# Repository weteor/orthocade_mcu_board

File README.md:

# orthocade series mcu board

this is a mcu daughterboard used for some keyboards from the orthocade series, namely [Dig Dug](https://github.com/weteor/DigDug), [Brk Out](https://github.com/weteor/BrkOut) and [Froggr](https://github.com/weteor/Froggr).

## Want/Need one?

production files can be found [here](./prod). The cases are designed for 1.2mm pcbs, but also work with  1.6mm pcbs without problems.

You will need the following parts to build one:

- 1x capacitor - 0805 - 100nF

- 3x resistor -  0805 - 10kOhm

- 1x PCA9555 or TCA9555 IO-Expander

- 1x 20pin 0.5mm pitch FCC/FCP Connector

- 1x either Seeed Xiao RP2040 or Seeed Xiao BLE controller

optionally if you want to use BLE w/ battery:

- 1x battery connectro 2pin Molex Pico Blade
- 1x on/off switch MSK-12C02

### the rest

Everything in this repository is free to use however you might see fit. If you want to support me and my projects, please consider linking back to this repository if you build/change/use anything.

If you would like to send me a tip, you could do it [here](https://ko-fi.com/weteor) (Please don't feel like you have to).

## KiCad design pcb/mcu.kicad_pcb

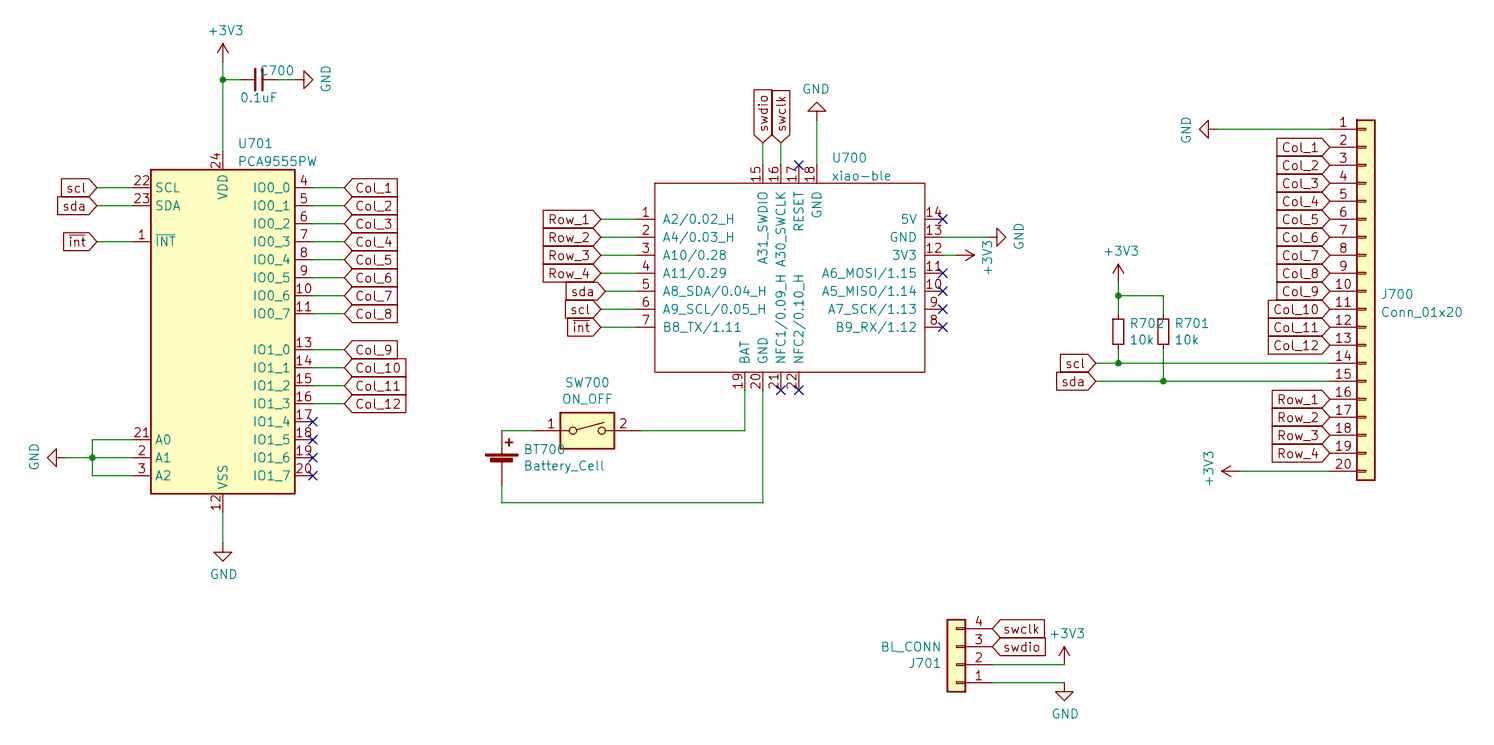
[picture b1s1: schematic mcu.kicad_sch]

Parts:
BT700: Battery_Cell; Molex_PicoBlade_53048-0210_1x02_P1.25mm_Horizontal
C700: 0.1uF; C_0805_2012Metric
J700: Conn_01x20; FCC 20pin
J701: BL_CONN; PinHeader_1x04_P2.54mm_Vertical
R701, R702: 10k; R_0805_2012Metric
SW700: ON_OFF; switch_MSK-12C02_smd
U700: xiao-ble; xiao-ble-smd-cutout
U701: PCA9555PW; TSSOP-24_4.4x7.8mm_P0.65mm

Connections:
+3V3: C700.2, J700.20, J701.2, R701.1, R702.1, U700.12 (3V3), U701.24 (VDD); also elsewhere on the board
Col_1: J700.2, U701.4 (IO0_0)
Col_2: J700.3, U701.5 (IO0_1)
Col_3: J700.4, U701.6 (IO0_2)
Col_4: J700.5, U701.7 (IO0_3)
Col_5: J700.6, U701.8 (IO0_4)
Col_6: J700.7, U701.9 (IO0_5)
Col_7: J700.8, U701.10 (IO0_6)
Col_8: J700.9, U701.11 (IO0_7)
Col_9: J700.10, U701.13 (IO1_0)
Col_10: J700.11, U701.14 (IO1_1)
Col_11: J700.12, U701.15 (IO1_2)
Col_12: J700.13, U701.16 (IO1_3)
GND: C700.1, J700.1, J701.1, U700.13 (GND), U700.18 (GND), U701.2 (A1), U701.3 (A2), U701.12 (VSS), U701.21 (A0)
unnamed: BT700.1 (+), SW700.1
unnamed: BT700.2 (-), U700.20 (GND)
unnamed 16: U700.7 (B8_TX/1.11), U701.1 (~INT); also elsewhere on the board
unnamed: SW700.2, U700.19 (BAT)
Row_1: J700.16, U700.1 (A2/0.02_H)
Row_2: J700.17, U700.2 (A4/0.03_H)
Row_3: J700.18, U700.3 (A10/0.28)
Row_4: J700.19, U700.4 (A11/0.29)
scl: J700.14, R702.2, U700.6 (A9_SCL/0.05_H), U701.22 (SCL)
sda: J700.15, R701.2, U700.5 (A8_SDA/0.04_H), U701.23 (SDA)
swclk: J701.4, U700.16 (A30_SWCLK)
swdio: J701.3, U700.15 (A31_SWDIO)

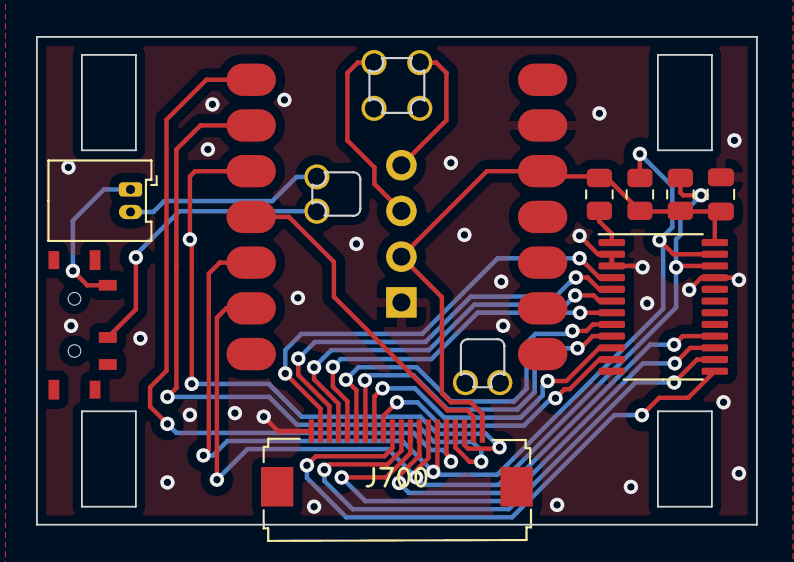
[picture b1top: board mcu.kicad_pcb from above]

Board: 2 copper layers, 40.0 x 27.1 mm, 10 parts (1 on the bottom side), 26 nets.

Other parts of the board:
R700: 10k; R_0805_2012Metric

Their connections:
+3V3: R700.1; also elsewhere on the board
unnamed 16: R700.2; also elsewhere on the board

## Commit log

2023-02-02 add cad files
2023-02-02 add gerber
2023-02-02 add readme
2023-02-02 Update LICENSE
